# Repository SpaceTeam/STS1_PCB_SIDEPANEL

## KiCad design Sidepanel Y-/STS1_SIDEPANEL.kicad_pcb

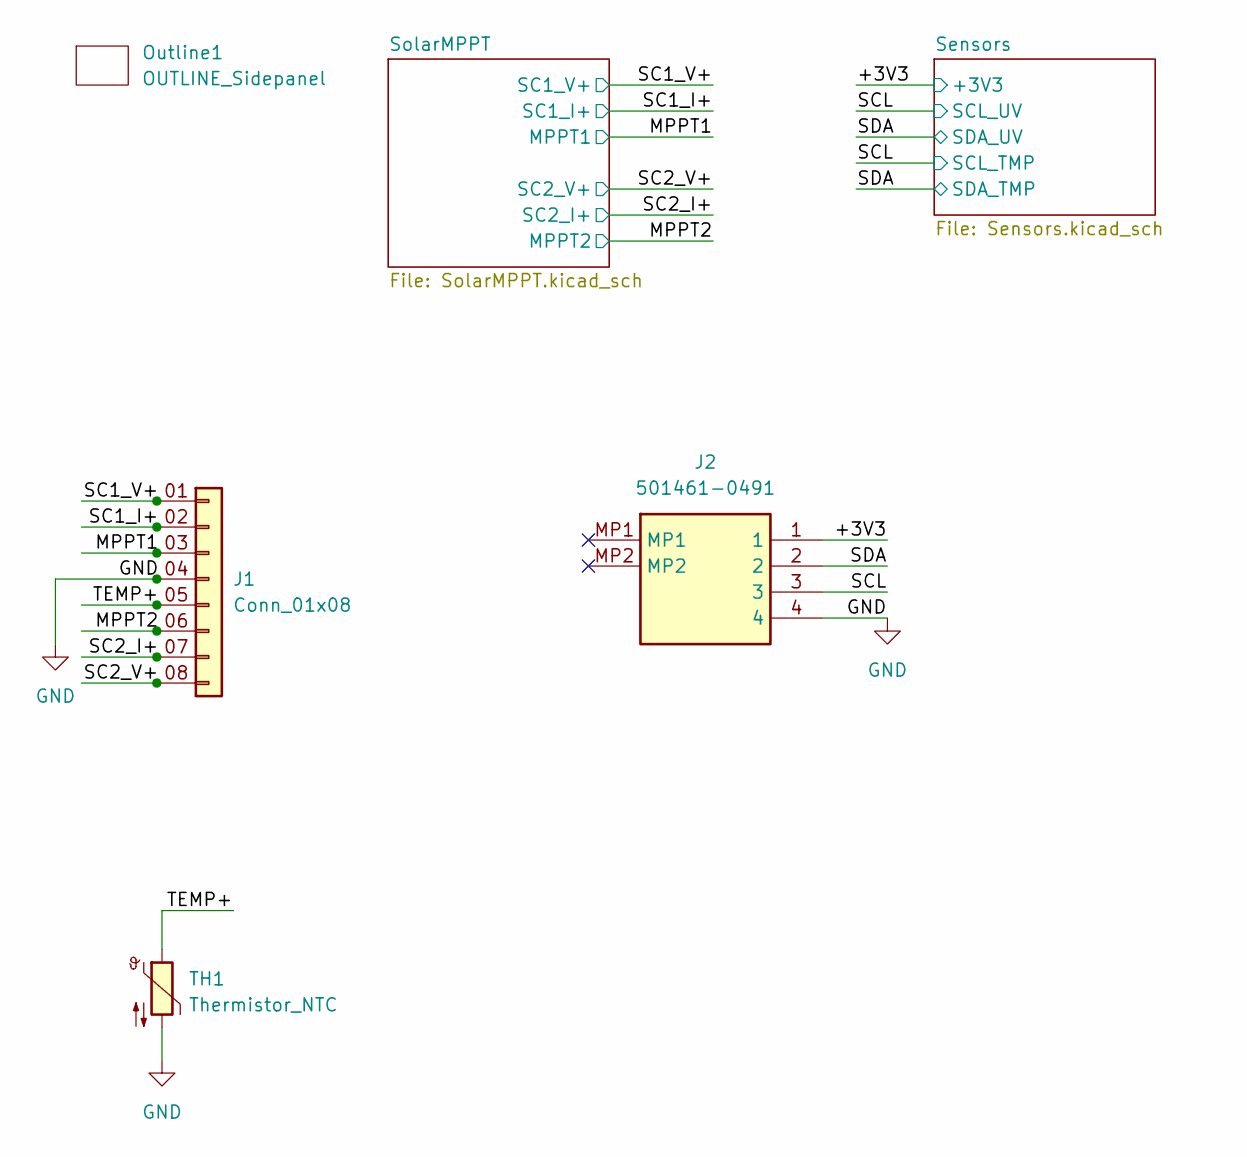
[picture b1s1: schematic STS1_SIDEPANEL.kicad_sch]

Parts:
J1: Conn_01x08; SAMTEC_ZF5S-08-01-T-WT
Outline1: OUTLINE_Sidepanel; OUTLINE_SidepanelY+
TH1: Thermistor_NTC; R_0805_2012Metric_Pad1.20x1.40mm_HandSolder
UV1: 501461-0491; 5014610491; Manufacturer_Part_Number 501461-0491; Mouser Part Number 538-501461-0491

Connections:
/+3V3: UV1.1; also elsewhere on the board
/MPPT1: J1.03 (Pin_3); also elsewhere on the board
/MPPT2: J1.06 (Pin_6); also elsewhere on the board
/SC1_I+: J1.02 (Pin_2); also elsewhere on the board
/SC1_V+: J1.01 (Pin_1); also elsewhere on the board
/SC2_I+: J1.07 (Pin_7); also elsewhere on the board
/SC2_V+: J1.08 (Pin_8); also elsewhere on the board
/SCL: UV1.3; also elsewhere on the board
/SDA: UV1.2; also elsewhere on the board
/TEMP+: J1.05 (Pin_5), TH1.1
GND: J1.04 (Pin_4), TH1.2, UV1.4; also elsewhere on the board

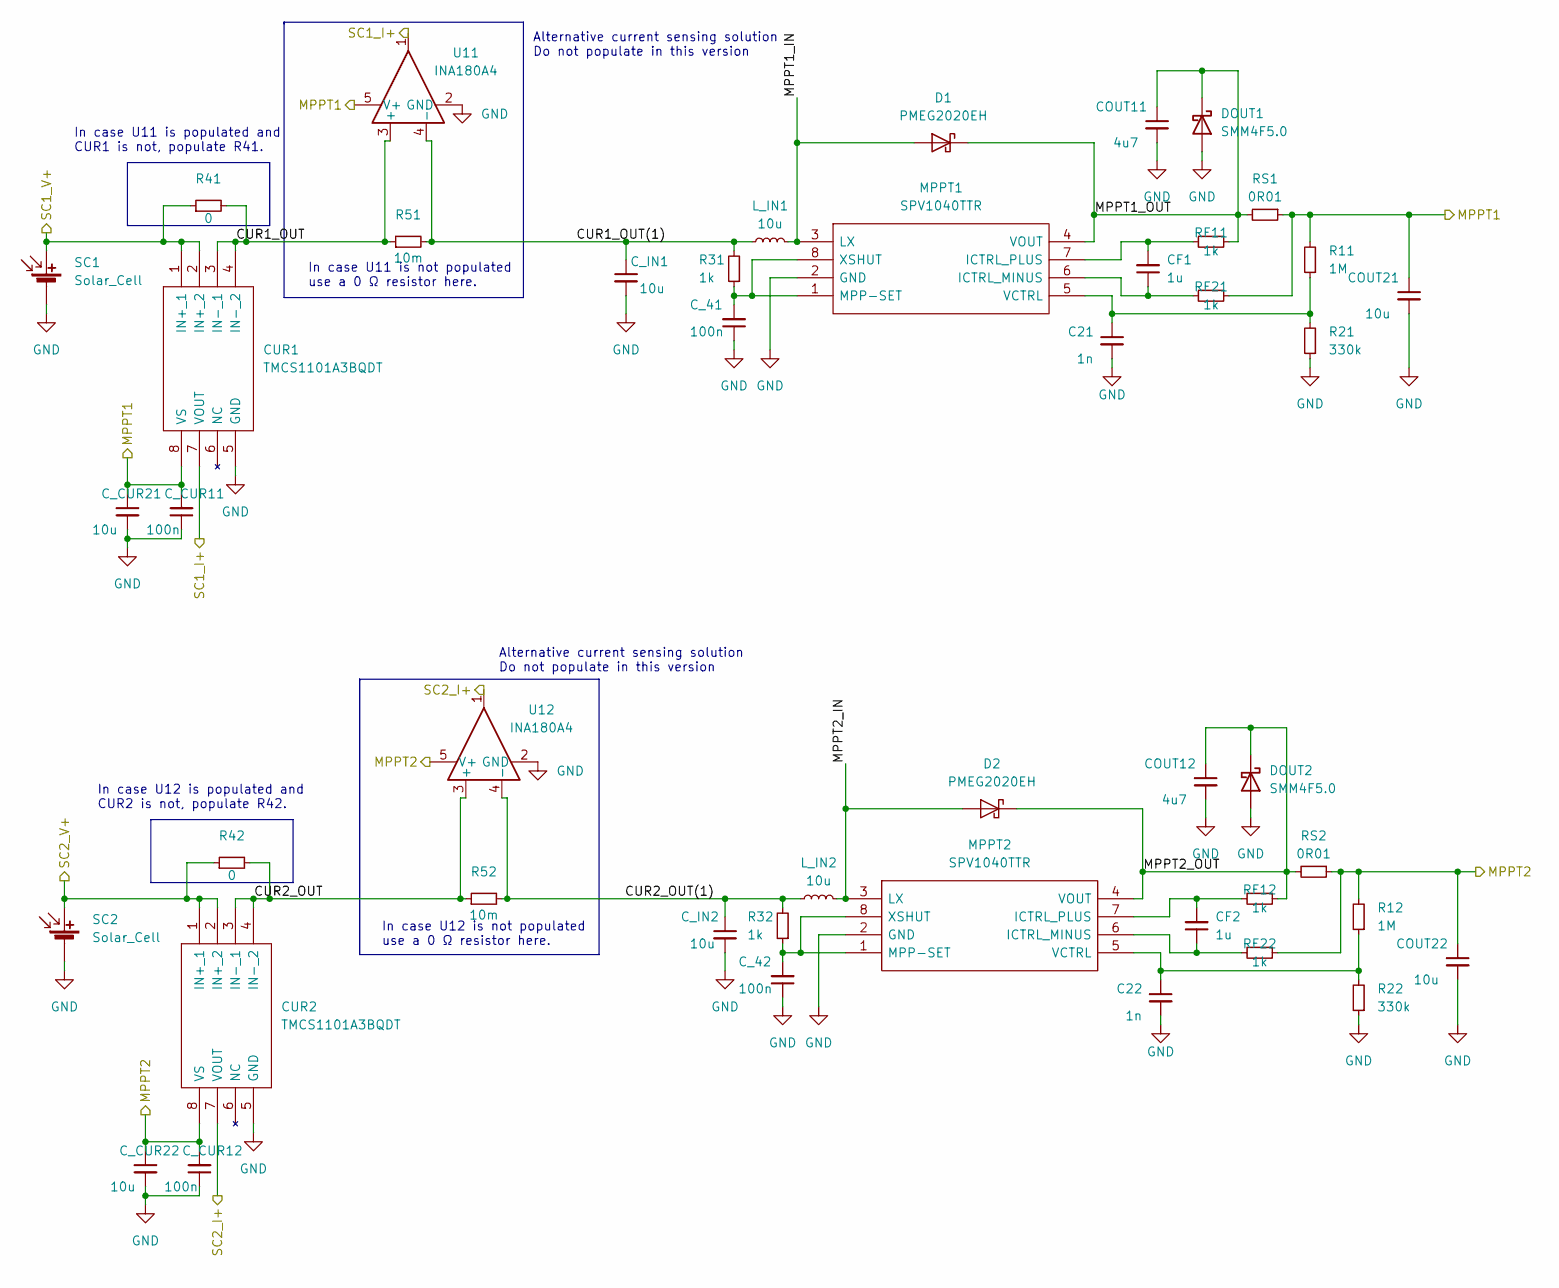
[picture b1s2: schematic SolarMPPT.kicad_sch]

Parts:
C21, C22: 1n; C_0603_1608Metric
CF1, CF2: 1u; C_0603_1608Metric
COUT11, COUT12: 4u7; C_0603_1608Metric
COUT21, COUT22: 10u; C_0603_1608Metric
CUR1, CUR2: TMCS1101A3BQDT; SOIC-8_3.9x4.9mm_P1.27mm; Mouser Part Number 595-TMCS1101A3BQDT
C_41, C_42: 100n; C_0603_1608Metric
C_CUR11, C_CUR12: 100n; C_0603_1608Metric
C_CUR21, C_CUR22: 10u; C_0603_1608Metric
C_IN1, C_IN2: 10u; C_0603_1608Metric
D1, D2: PMEG2020EH; D_SOD-123F
DOUT1, DOUT2: SMM4F5.0; STMITE
L_IN1, L_IN2: 10u; XAL6060103MEC
MPPT1, MPPT2: SPV1040TTR; TSSOP-8_4.4x3mm_P0.65mm; Mouser Part Number 511-SPV1040TTR
R11, R12: 1M; R_0603_1608Metric
R21, R22: 330k; R_0603_1608Metric
R31, R32: 1k; R_0603_1608Metric
R41, R42: 0; R_0603_1608Metric
R51, R52: 10m; R_0603_1608Metric
RF11, RF12, RF21, RF22: 1k; R_0603_1608Metric
RS1, RS2: 0R01; R_0603_1608Metric
SC1: Solar_Cell; 3G30A_40x80_Y_SC1
SC2: Solar_Cell; 3G30A_40x80_Y_SC2
U11, U12: INA180A4; SOT-23-5

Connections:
/MPPT1: COUT21.1, CUR1.8 (VS), C_CUR11.2, C_CUR21.1, R11.2, RF21.1, RS1.1, U11.5 (V+); also elsewhere on the board
/MPPT2: COUT22.1, CUR2.8 (VS), C_CUR12.2, C_CUR22.1, R12.2, RF22.1, RS2.1, U12.5 (V+); also elsewhere on the board
/SC1_I+: CUR1.7 (VOUT), U11.1; also elsewhere on the board
/SC1_V+: CUR1.1 (IN+_1), CUR1.2 (IN+_2), R41.1, SC1.1 (+), SC1.4; also elsewhere on the board
/SC2_I+: CUR2.7 (VOUT), U12.1; also elsewhere on the board
/SC2_V+: CUR2.1 (IN+_1), CUR2.2 (IN+_2), R42.1, SC2.1 (+), SC2.4; also elsewhere on the board
/SolarMPPT/CUR1_OUT: CUR1.3 (IN-_1), CUR1.4 (IN-_2), R41.2, R51.1, U11.3 (+)
/SolarMPPT/CUR1_OUT(1): C_IN1.1, L_IN1.1, R31.2, R51.2, U11.4 (-)
/SolarMPPT/CUR2_OUT: CUR2.3 (IN-_1), CUR2.4 (IN-_2), R42.2, R52.1, U12.3 (+)
/SolarMPPT/CUR2_OUT(1): C_IN2.1, L_IN2.1, R32.2, R52.2, U12.4 (-)
/SolarMPPT/MPPT1_IN: D1.2 (A), L_IN1.2, MPPT1.3 (LX)
/SolarMPPT/MPPT1_OUT: COUT11.1, D1.1 (K), DOUT1.1 (K), MPPT1.4 (VOUT), RF11.1, RS1.2
/SolarMPPT/MPPT2_IN: D2.2 (A), L_IN2.2, MPPT2.3 (LX)
/SolarMPPT/MPPT2_OUT: COUT12.1, D2.1 (K), DOUT2.1 (K), MPPT2.4 (VOUT), RF12.1, RS2.2
GND: C21.2, C22.2, COUT11.2, COUT12.2, COUT21.2, COUT22.2, CUR1.5 (GND), CUR2.5 (GND), C_41.1, C_42.1, C_CUR11.1, C_CUR12.1, C_CUR21.2, C_CUR22.2, C_IN1.2, C_IN2.2, DOUT1.2 (A), DOUT2.2 (A), MPPT1.2 (GND), MPPT2.2 (GND), R21.1, R22.1, SC1.2 (-), SC2.2 (-), U11.2 (GND), U12.2 (GND); also elsewhere on the board
unnamed: C21.1, MPPT1.5 (VCTRL), R11.1, R21.2
unnamed: C22.1, MPPT2.5 (VCTRL), R12.1, R22.2
unnamed: CF1.1, MPPT1.6 (ICTRL_MINUS), RF21.2
unnamed: CF1.2, MPPT1.7 (ICTRL_PLUS), RF11.2
unnamed: CF2.1, MPPT2.6 (ICTRL_MINUS), RF22.2
unnamed: CF2.2, MPPT2.7 (ICTRL_PLUS), RF12.2
unnamed: C_41.2, MPPT1.1 (MPP-SET), MPPT1.8 (XSHUT), R31.1
unnamed: C_42.2, MPPT2.1 (MPP-SET), MPPT2.8 (XSHUT), R32.1

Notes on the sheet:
Alternative current sensing solution Do not populate in this version
In case U11 is not populated use a 0 Ω resistor here.
In case U12 is not populated use a 0 Ω resistor here.
In case U11 is populated and CUR1 is not, populate R41.
In case U12 is populated and CUR2 is not, populate R42.

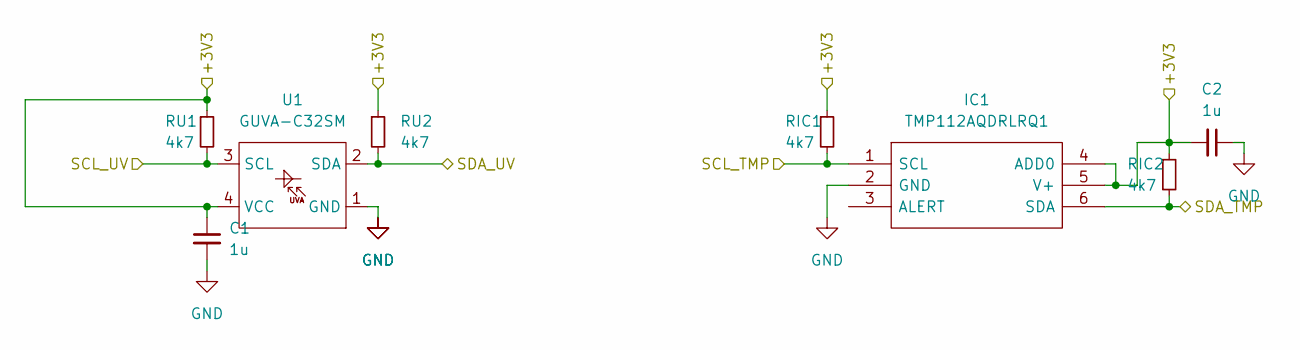
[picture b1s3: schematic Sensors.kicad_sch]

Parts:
C1, C2: 1u; C_0603_1608Metric
IC1: TMP112AQDRLRQ1; SOT-563; Mouser Part Number 595-TMP112AQDRLRQ1
RIC1, RIC2: 4k7; R_0603_1608Metric
RU1, RU2: 4k7; R_0603_1608Metric
U1: GUVA-C32SM; SO-4_4.4x3.6mm_P2.54mm

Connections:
/+3V3: C1.1, C2.2, IC1.4 (ADD0), IC1.5 (V+), RIC1.1, RIC2.1, RU1.1, RU2.1, U1.4 (VCC); also elsewhere on the board
/SCL: IC1.1 (SCL), RIC1.2, RU1.2, U1.3 (SCL); also elsewhere on the board
/SDA: IC1.6 (SDA), RIC2.2, RU2.2, U1.2 (SDA); also elsewhere on the board
GND: C1.2, C2.1, IC1.2 (GND), IC1.3 (ALERT), U1.1 (GND); also elsewhere on the board

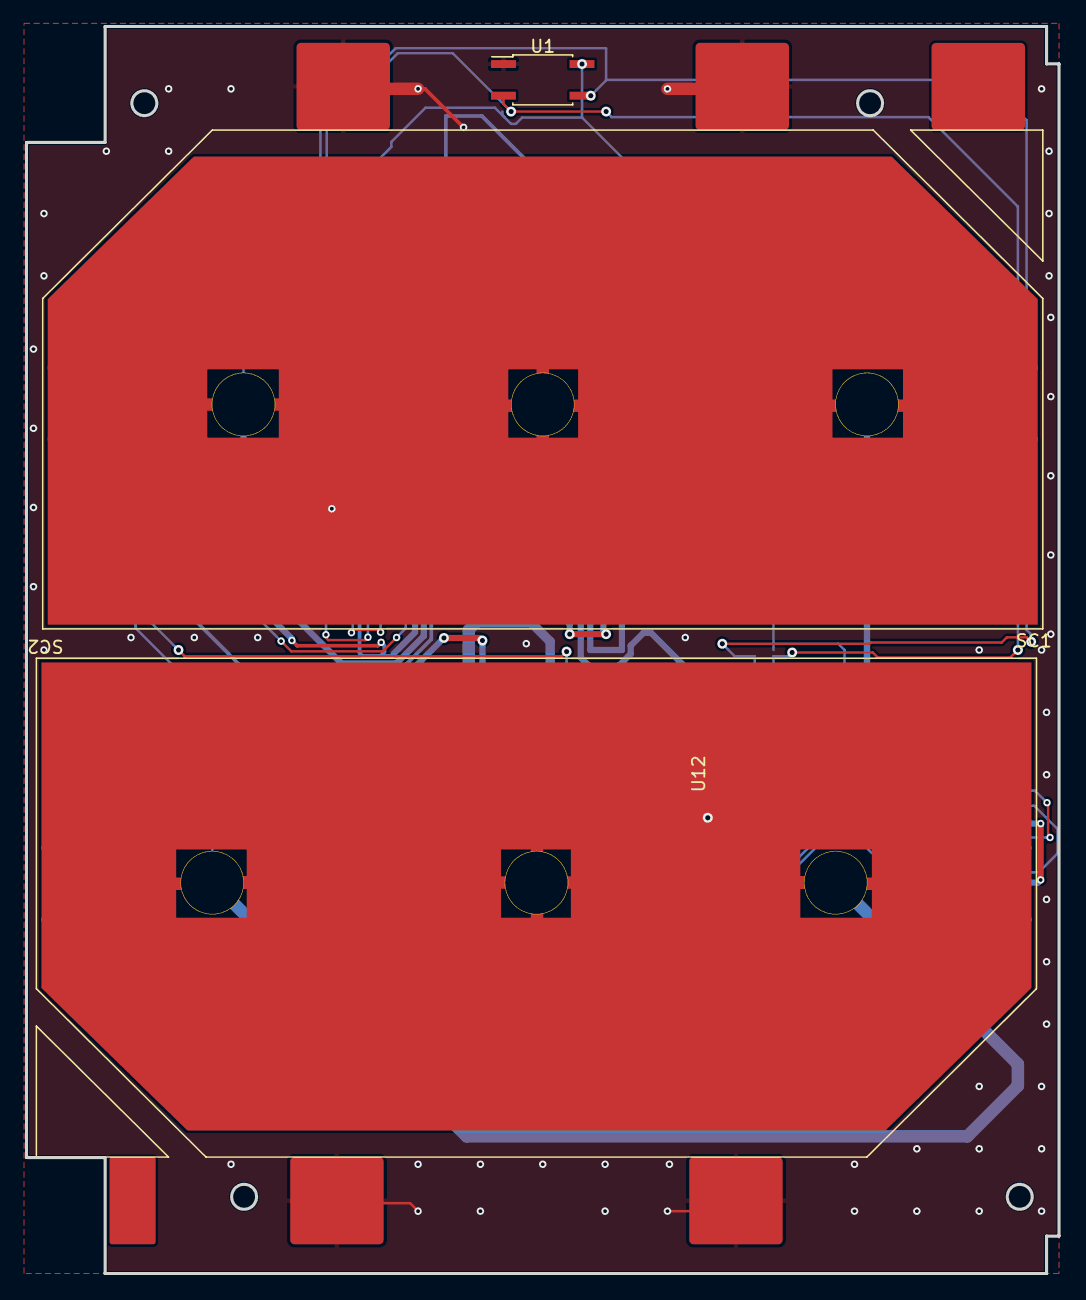
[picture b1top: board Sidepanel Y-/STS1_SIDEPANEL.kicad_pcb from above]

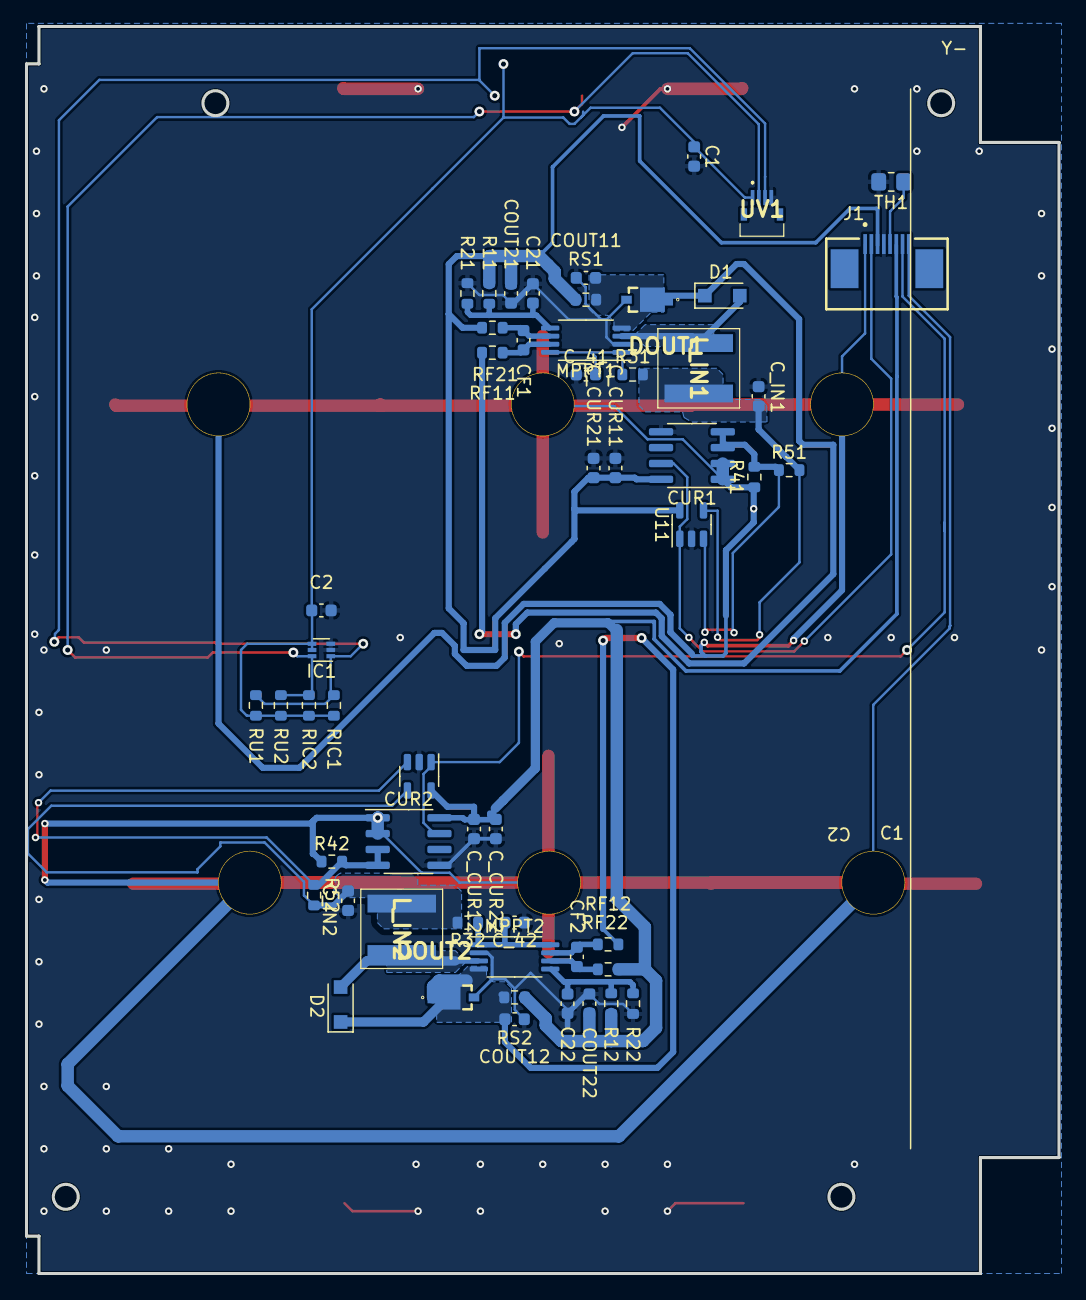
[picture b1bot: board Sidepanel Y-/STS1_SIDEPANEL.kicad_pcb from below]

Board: 2 copper layers, 82.8 x 100.0 mm, 58 parts (54 on the bottom side), 27 nets.

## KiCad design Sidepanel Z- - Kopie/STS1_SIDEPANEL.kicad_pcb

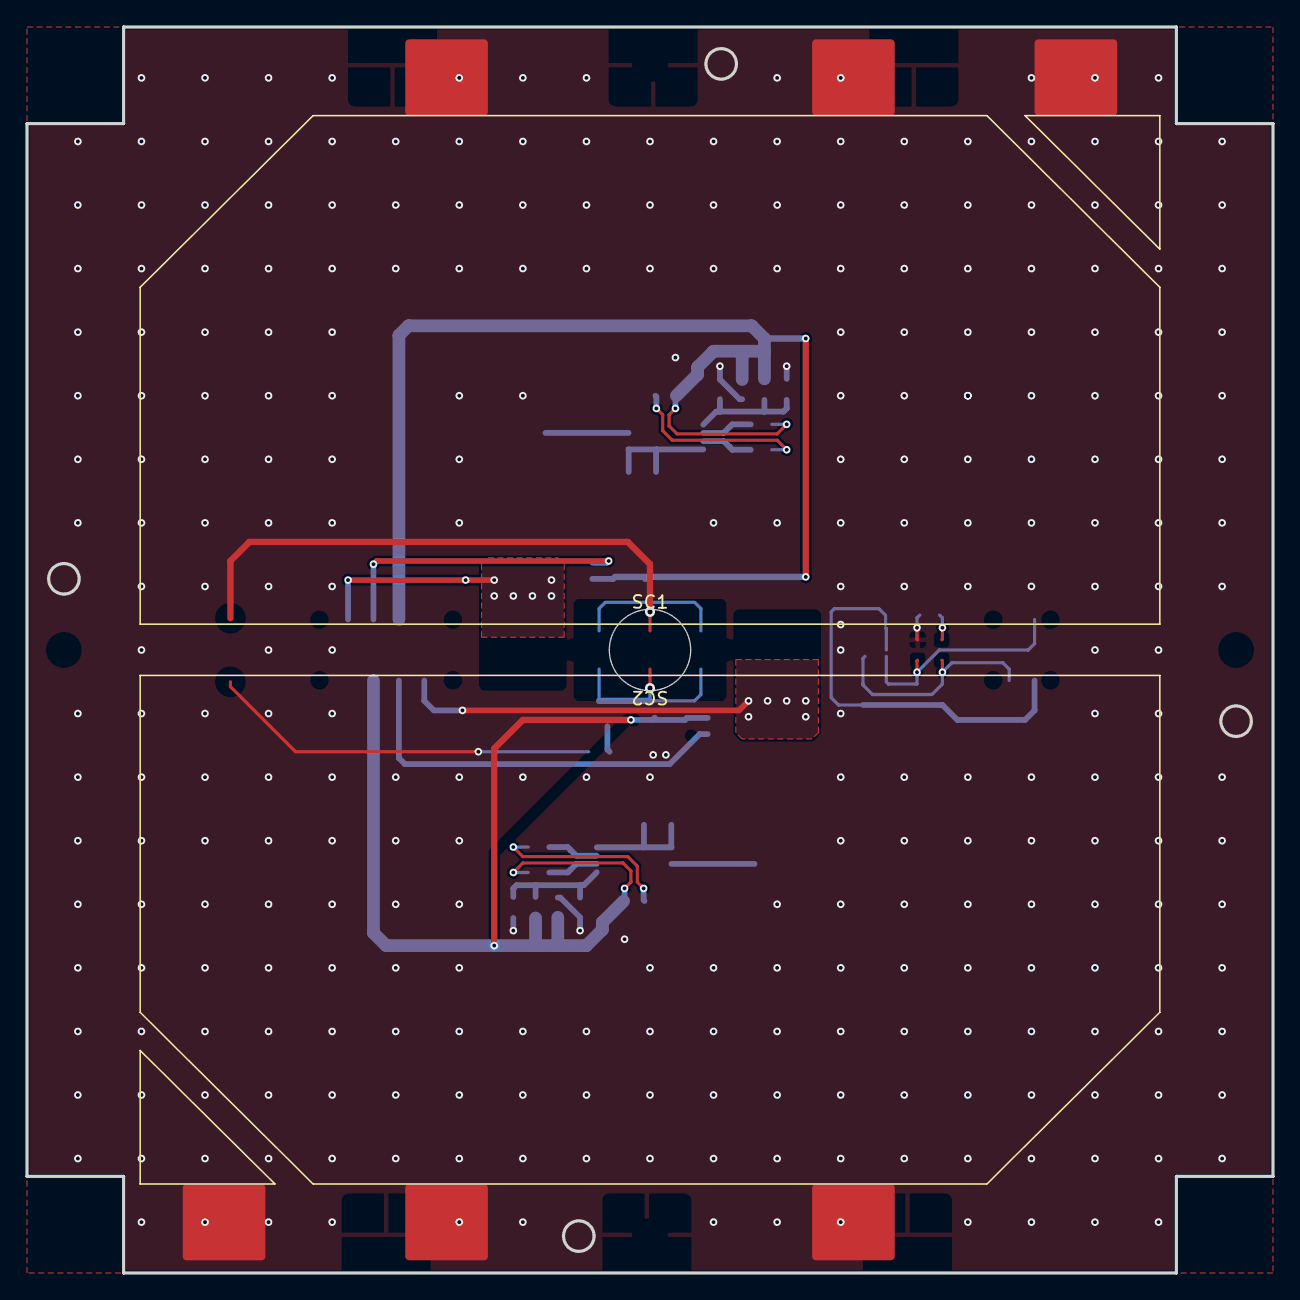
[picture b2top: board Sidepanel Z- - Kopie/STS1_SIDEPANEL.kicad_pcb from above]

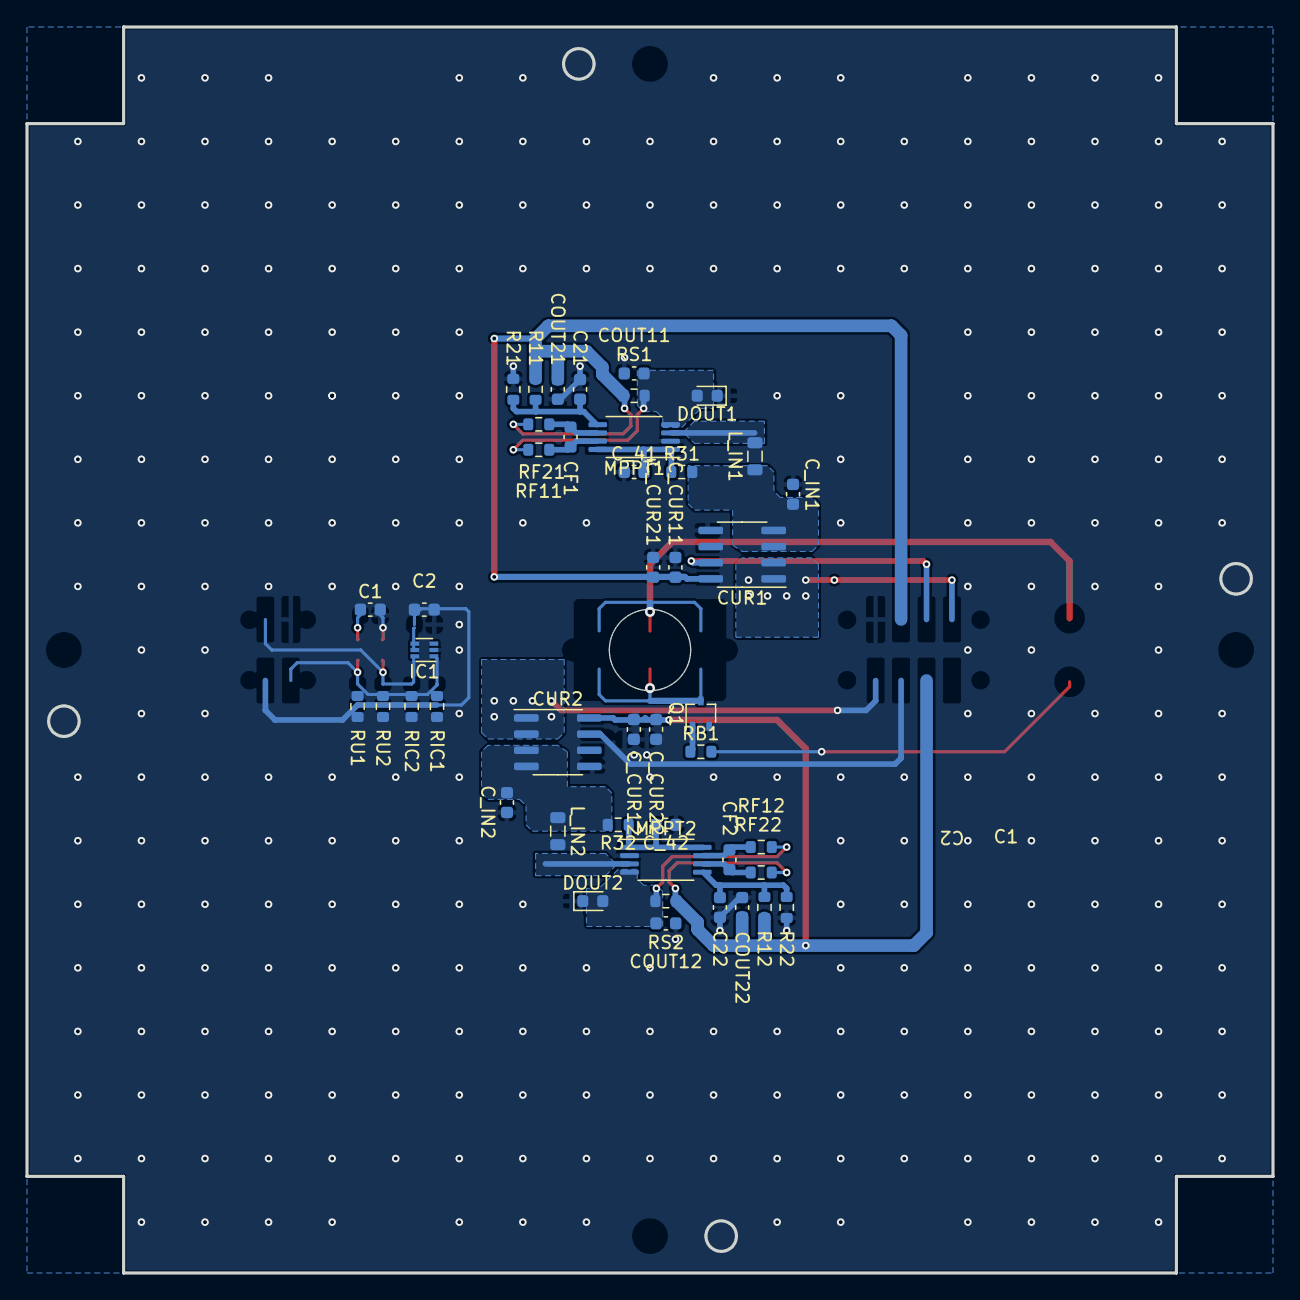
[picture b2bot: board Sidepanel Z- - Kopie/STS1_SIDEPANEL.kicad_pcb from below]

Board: 2 copper layers, 98.0 x 98.0 mm, 48 parts (45 on the bottom side), 23 nets.

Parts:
C1, C2: 1u; C_0603_1608Metric
C21, C22: 1n; C_0603_1608Metric
CF1, CF2: 1u; C_0603_1608Metric
COUT11, COUT12: 4u7; C_0603_1608Metric
COUT21, COUT22: 10u; C_0603_1608Metric
CUR1, CUR2: TMCS1101A3BQDT; SOIC-8_3.9x4.9mm_P1.27mm
C_41, C_42: 100n; C_0603_1608Metric
C_CUR11, C_CUR12: 100n; C_0603_1608Metric
C_CUR21, C_CUR22: 10u; C_0603_1608Metric
C_IN1, C_IN2: 10u; C_0603_1608Metric
DOUT1: SMM4F5.0; D_0603_1608Metric
DOUT2: SMM4F5.0; LED_0603_1608Metric
IC1: TMP112AQDRLRQ1; SOT-563
L_IN1, L_IN2: 10u; L_0805_2012Metric
MPPT1, MPPT2: SPV1040TTR; TSSOP-8_4.4x3mm_P0.65mm
Outline1: OUTLINE_Sidepanel; OUTLINE_SidepanelZ+
Q1: BSS214NW; SOT-323_SC-70
R11, R12: 1M; R_0603_1608Metric
R21, R22: tbd; R_0603_1608Metric
R31, R32: 1k; R_0603_1608Metric
RB1: 10k; R_0603_1608Metric
RF11, RF12, RF21, RF22: 1k; R_0603_1608Metric
RIC1, RIC2: 4k7; R_0603_1608Metric
RS1, RS2: 0R01; R_0603_1608Metric
RU1, RU2: 4k7; R_0603_1608Metric
SC1, SC2: Solar_Cell; 3G30A_40x80

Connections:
/+3V3: C2.2, IC1.4 (ADD0), IC1.5 (V+), RIC1.1, RIC2.1, RU1.1, RU2.1
/MPPT1: COUT21.1, CUR1.8 (VS), C_CUR11.2, C_CUR21.1, R11.2, RF21.1, RS1.1
/MPPT2: COUT22.1, CUR2.8 (VS), C_CUR12.2, C_CUR22.1, R12.2, RF22.1, RS2.1
/SC1_V+: CUR1.1 (IN+_1), CUR1.2 (IN+_2), SC1.1 (+)
/SC2_V+: CUR2.1 (IN+_1), CUR2.2 (IN+_2), SC2.1 (+)
/SCL: IC1.1 (SCL), RIC1.2, RU1.2
/SDA: IC1.6 (SDA), RIC2.2, RU2.2
/SolarMPPT/CUR1_OUT: CUR1.3 (IN-_1), CUR1.4 (IN-_2), C_IN1.1, L_IN1.1, R31.2
/SolarMPPT/CUR2_OUT: CUR2.3 (IN-_1), CUR2.4 (IN-_2), C_IN2.1, L_IN2.1, R32.2
/SolarMPPT/MPPT1_IN: L_IN1.2, MPPT1.3 (LX)
/SolarMPPT/MPPT1_OUT: COUT11.1, DOUT1.1 (K), MPPT1.4 (VOUT), RF11.1, RS1.2
/SolarMPPT/MPPT2_IN: L_IN2.2, MPPT2.3 (LX)
/SolarMPPT/MPPT2_OUT: COUT12.1, DOUT2.1 (K), MPPT2.4 (VOUT), RF12.1, RS2.2
GND: C1.2, C2.1, C21.2, C22.2, COUT11.2, COUT12.2, COUT21.2, COUT22.2, CUR1.5 (GND), CUR2.5 (GND), C_41.1, C_42.1, C_CUR11.1, C_CUR12.1, C_CUR21.2, C_CUR22.2, C_IN1.2, C_IN2.2, DOUT1.2 (A), DOUT2.2 (A), IC1.2 (GND), MPPT1.2 (GND), MPPT2.2 (GND), Q1.2 (S), R21.1, R22.1, SC1.2 (-), SC2.2 (-)
unnamed: C21.1, MPPT1.5 (VCTRL), R11.1, R21.2
unnamed: C22.1, MPPT2.5 (VCTRL), R12.1, R22.2
unnamed: CF1.1, MPPT1.6 (ICTRL_MINUS), RF21.2
unnamed: CF1.2, MPPT1.7 (ICTRL_PLUS), RF11.2
unnamed: CF2.1, MPPT2.6 (ICTRL_MINUS), RF22.2
unnamed: CF2.2, MPPT2.7 (ICTRL_PLUS), RF12.2
unnamed: C_41.2, MPPT1.1 (MPP-SET), MPPT1.8 (XSHUT), R31.1
unnamed: C_42.2, MPPT2.1 (MPP-SET), MPPT2.8 (XSHUT), R32.1
unnamed: Q1.1 (G), RB1.1
